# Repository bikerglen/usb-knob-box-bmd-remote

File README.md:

# usb-knob-box-bmd-remote

Blog post describing this project: https://bikerglen.com/blog/usb-knobs-that-double-as-a-blackmagic-remote/

If using the C# .NET app for testing, the product ID needs to be set to 0x0014 for the EFM8UB@ version or 0x0015 for the PIC18 version. This is inside the file Form1.cs.

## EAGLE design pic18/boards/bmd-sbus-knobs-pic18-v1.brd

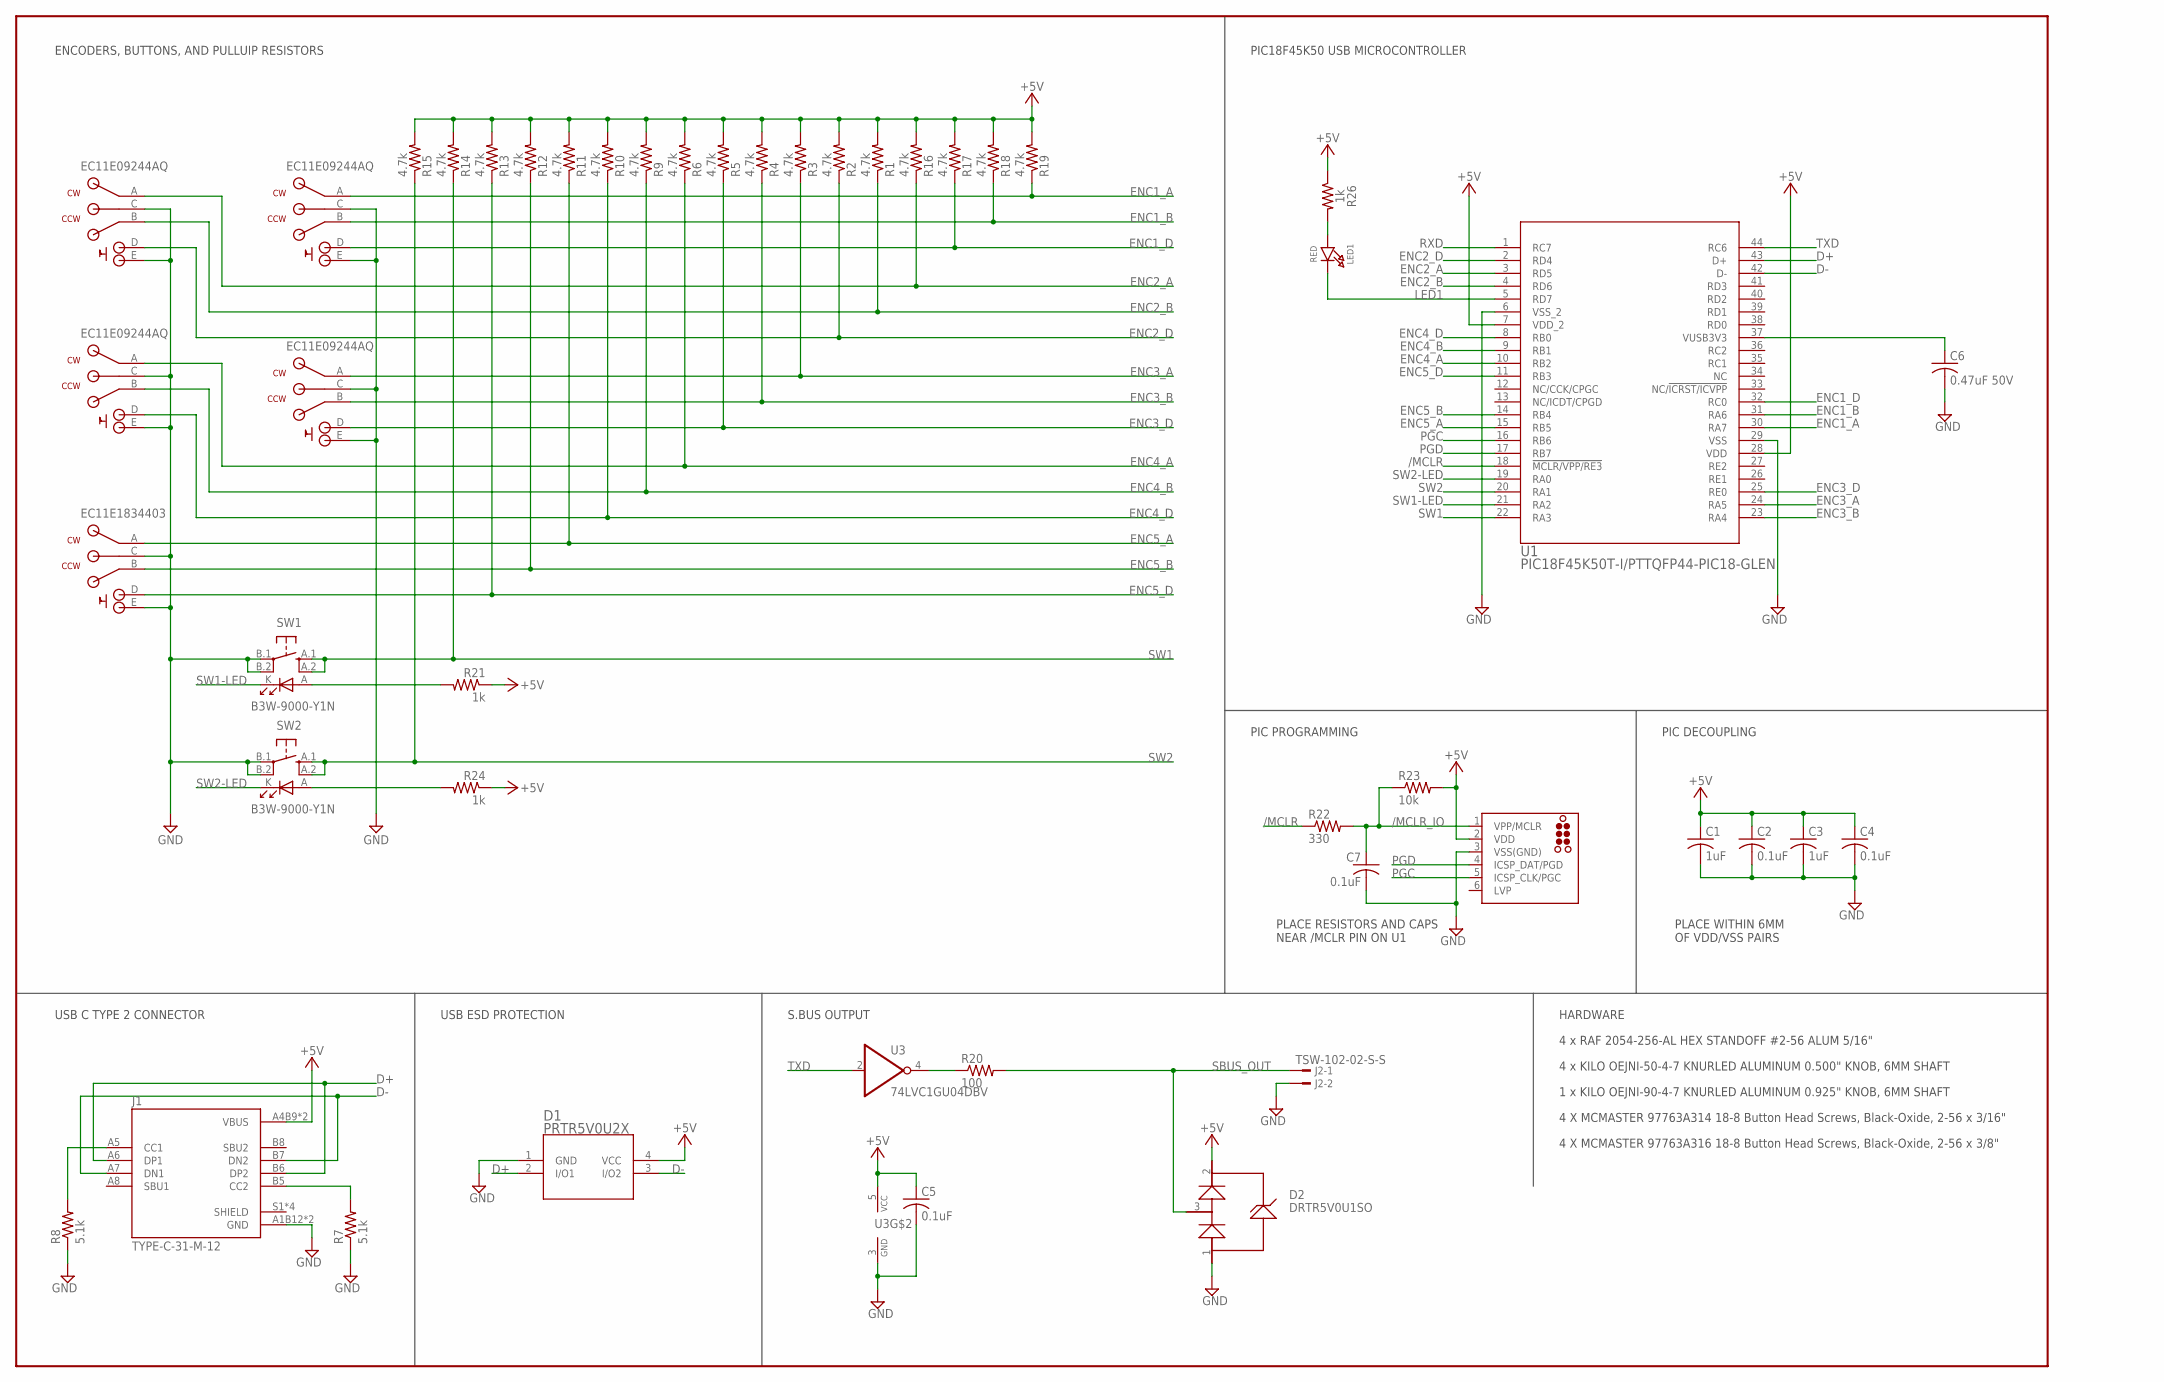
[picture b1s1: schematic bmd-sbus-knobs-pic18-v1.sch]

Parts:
C1, C3: 1uF; C0603K
C2, C4, C7: 0.1uF; C0603K
C5: 0.1uF; C0603
C6: 0.47uF 50V; C1206K; MFR_PART_NO C1206C474K5RACTU
D1: PRTR5V0U2X; SOT143B
D2: DRTR5V0U1SO; SOT23-3; MFR_PART_NO DRTR5V0U1SO
DEBUG: TC2030-MCP-NL
ENC1, ENC2, ENC3, ENC4, ENC5: EC11E15244B2
J1: TYPE-C-31-M-12; HRO_TYPE-C-31-M-12
J2: TSW-102-02-S-S
LED1: RED; CHIPLED_0805_NOOUTLINE
R1, R2, R3, R4, R5, R6, R9, R10, R11, R12, R13, R14, R15, R16, R17, R18, R19: 4.7k; R0603
R7, R8: 5.1k; R0603
R20: 100; R0603
R21, R24, R26: 1k; R0603
R22: 330; R0603
R23: 10k; R0603
SW1, SW2: B3W-9000-Y1N; OMRON-B3W-ILLUM-BUTTON
U1: PIC18F45K50T-I/PTTQFP44-PIC18-GLEN; TQFP44-PIC18-GLEN
U3: 74LVC1GU04DBV; SOT23-5

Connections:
+5V: C1.1, C2.1, C3.1, C4.1, C5.1, D1.4 (VCC), D2.2, DEBUG.2 (VDD), J1.A4B9 (VBUS), J1.B4A9 (VBUS), R1.2, R2.2, R3.2, R4.2, R5.2, R6.2, R9.2, R10.2, R11.2, R12.2, R13.2, R14.2, R15.2, R16.2, R17.2, R18.2, R19.2, R21.1, R23.2, R24.1, R26.1, U1.7 (VDD_2), U1.28 (VDD), U3.5 (VCC)
/MCLR: R22.1, U1.18 (!MCLR/VPP/RE3)
/MCLR_IO: C7.1, DEBUG.1 (VPP/MCLR), R22.2, R23.1
CC1: J1.A5 (CC1), R8.2
CC2: J1.B5 (CC2), R7.2
D+: D1.2 (I/O1), J1.A6 (DP1), J1.B6 (DP2), U1.43 (D+)
D-: D1.3 (I/O2), J1.A7 (DN1), J1.B7 (DN2), U1.42 (D-)
ENC1_A: ENC1.A, R19.1, U1.30 (RA7)
ENC1_B: ENC1.B, R18.1, U1.31 (RA6)
ENC1_D: ENC1.D, R17.1, U1.32 (RC0)
ENC2_A: ENC2.A, R16.1, U1.3 (RD5)
ENC2_B: ENC2.B, R1.1, U1.4 (RD6)
ENC2_D: ENC2.D, R2.1, U1.2 (RD4)
ENC3_A: ENC3.A, R3.1, U1.24 (RA5)
ENC3_B: ENC3.B, R4.1, U1.23 (RA4)
ENC3_D: ENC3.D, R5.1, U1.25 (RE0)
ENC4_A: ENC4.A, R6.1, U1.10 (RB2)
ENC4_B: ENC4.B, R9.1, U1.9 (RB1)
ENC4_D: ENC4.D, R10.1, U1.8 (RB0)
ENC5_A: ENC5.A, R11.1, U1.15 (RB5)
ENC5_B: ENC5.B, R12.1, U1.14 (RB4)
ENC5_D: ENC5.D, R13.1, U1.11 (RB3)
GND: C1.2, C2.2, C3.2, C4.2, C5.2, C6.2, C7.2, D1.1 (GND), D2.1 (3), DEBUG.3 (VSS(GND)), ENC1.C, ENC1.E, ENC2.C, ENC2.E, ENC3.C, ENC3.E, ENC4.C, ENC4.E, ENC5.C, ENC5.E, J1.A1B12 (GND), J1.B1A12 (GND), J2.2, R7.1, R8.1, SW1.B.1, SW1.B.2, SW2.B.1, SW2.B.2, U1.6 (VSS_2), U1.29 (VSS), U3.3 (GND)
LED1: LED1.C, U1.5 (RD7)
unnamed: R20.1, U3.4 (O)
unnamed: LED1.A, R26.2
unnamed: R21.2, SW1.A
unnamed: R24.2, SW2.A
PGC: DEBUG.5 (ICSP_CLK/PGC), U1.16 (RB6)
PGD: DEBUG.4 (ICSP_DAT/PGD), U1.17 (RB7)
RXD: U1.1 (RC7)
SBUS_OUT: D2.3 (1), J2.1, R20.2
SW1: R14.1, SW1.A.1, SW1.A.2, U1.22 (RA3)
SW1-LED: SW1.K, U1.21 (RA2)
SW2: R15.1, SW2.A.1, SW2.A.2, U1.20 (RA1)
SW2-LED: SW2.K, U1.19 (RA0)
TXD: U1.44 (RC6), U3.2 (I)
VUSB: C6.1, U1.37 (VUSB3V3)

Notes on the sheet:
EC11E09244AQ
EC11E1834403
PIC DECOUPLING
USB C TYPE 2 CONNECTOR
USB ESD PROTECTION
PIC PROGRAMMING
S.BUS OUTPUT
PLACE WITHIN 6MM OF VDD/VSS PAIRS
HARDWARE
4 x RAF 2054-256-AL HEX STANDOFF #2-56 ALUM 5/16"
4 x KILO OEJNI-50-4-7 KNURLED ALUMINUM 0.500" KNOB, 6MM SHAFT
1 x KILO OEJNI-90-4-7 KNURLED ALUMINUM 0.925" KNOB, 6MM SHAFT
4 X MCMASTER 97763A314 18-8 Button Head Screws, Black-Oxide, 2-56 x 3/16"
4 X MCMASTER 97763A316 18-8 Button Head Screws, Black-Oxide, 2-56 x 3/8"
PLACE RESISTORS AND CAPS NEAR /MCLR PIN ON U1
ENCODERS, BUTTONS, AND PULLUIP RESISTORS
PIC18F45K50 USB MICROCONTROLLER

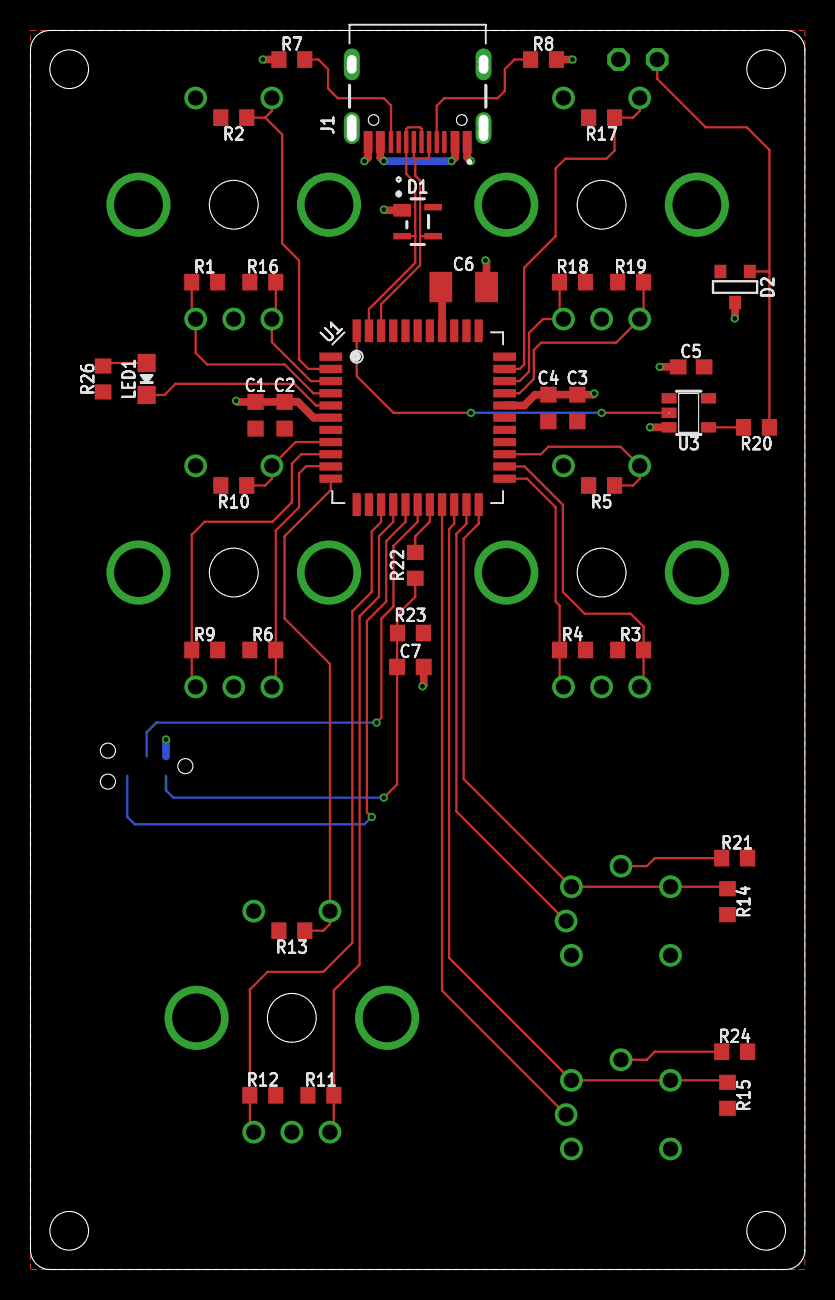
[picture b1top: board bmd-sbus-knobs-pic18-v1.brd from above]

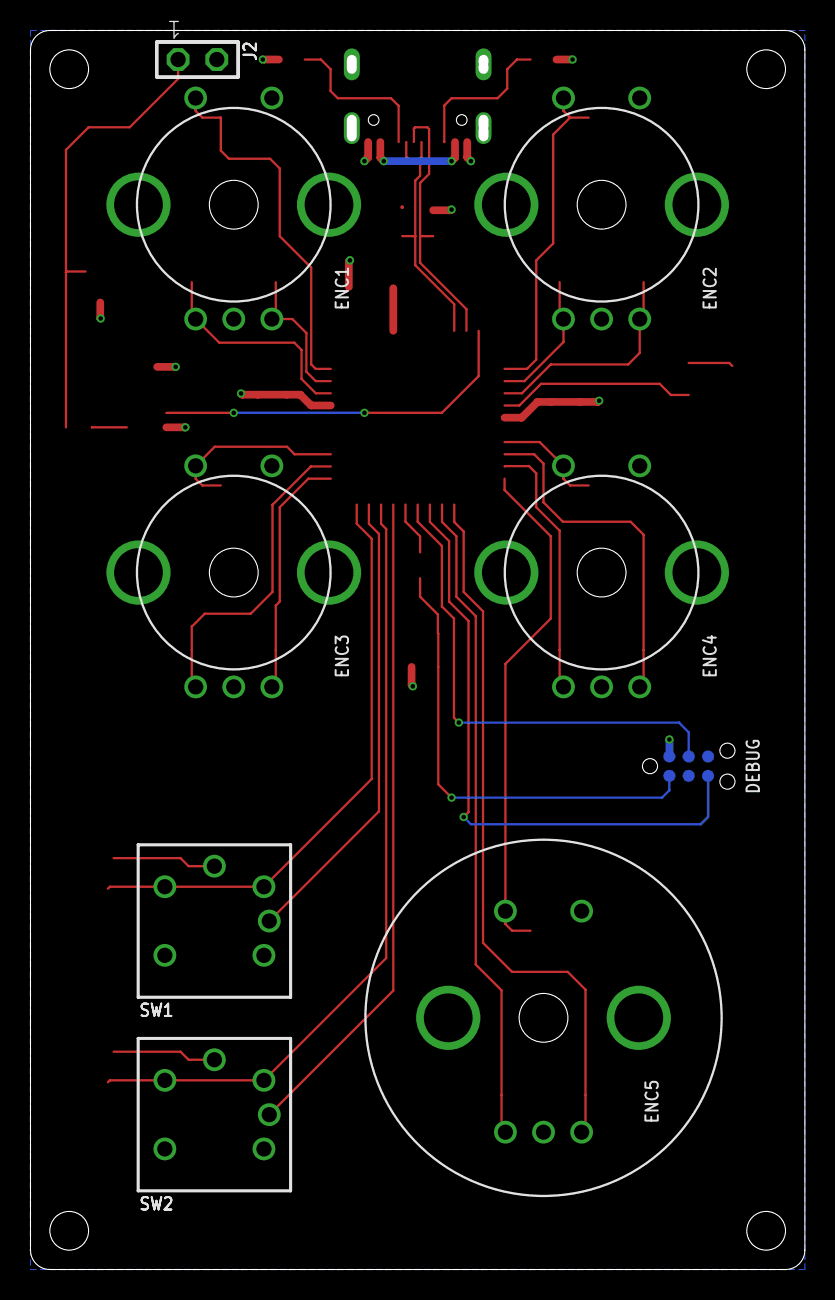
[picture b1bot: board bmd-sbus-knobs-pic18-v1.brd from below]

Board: 2 copper layers, 50.1 x 80.6 mm, 47 parts (9 on the bottom side), 37 nets.

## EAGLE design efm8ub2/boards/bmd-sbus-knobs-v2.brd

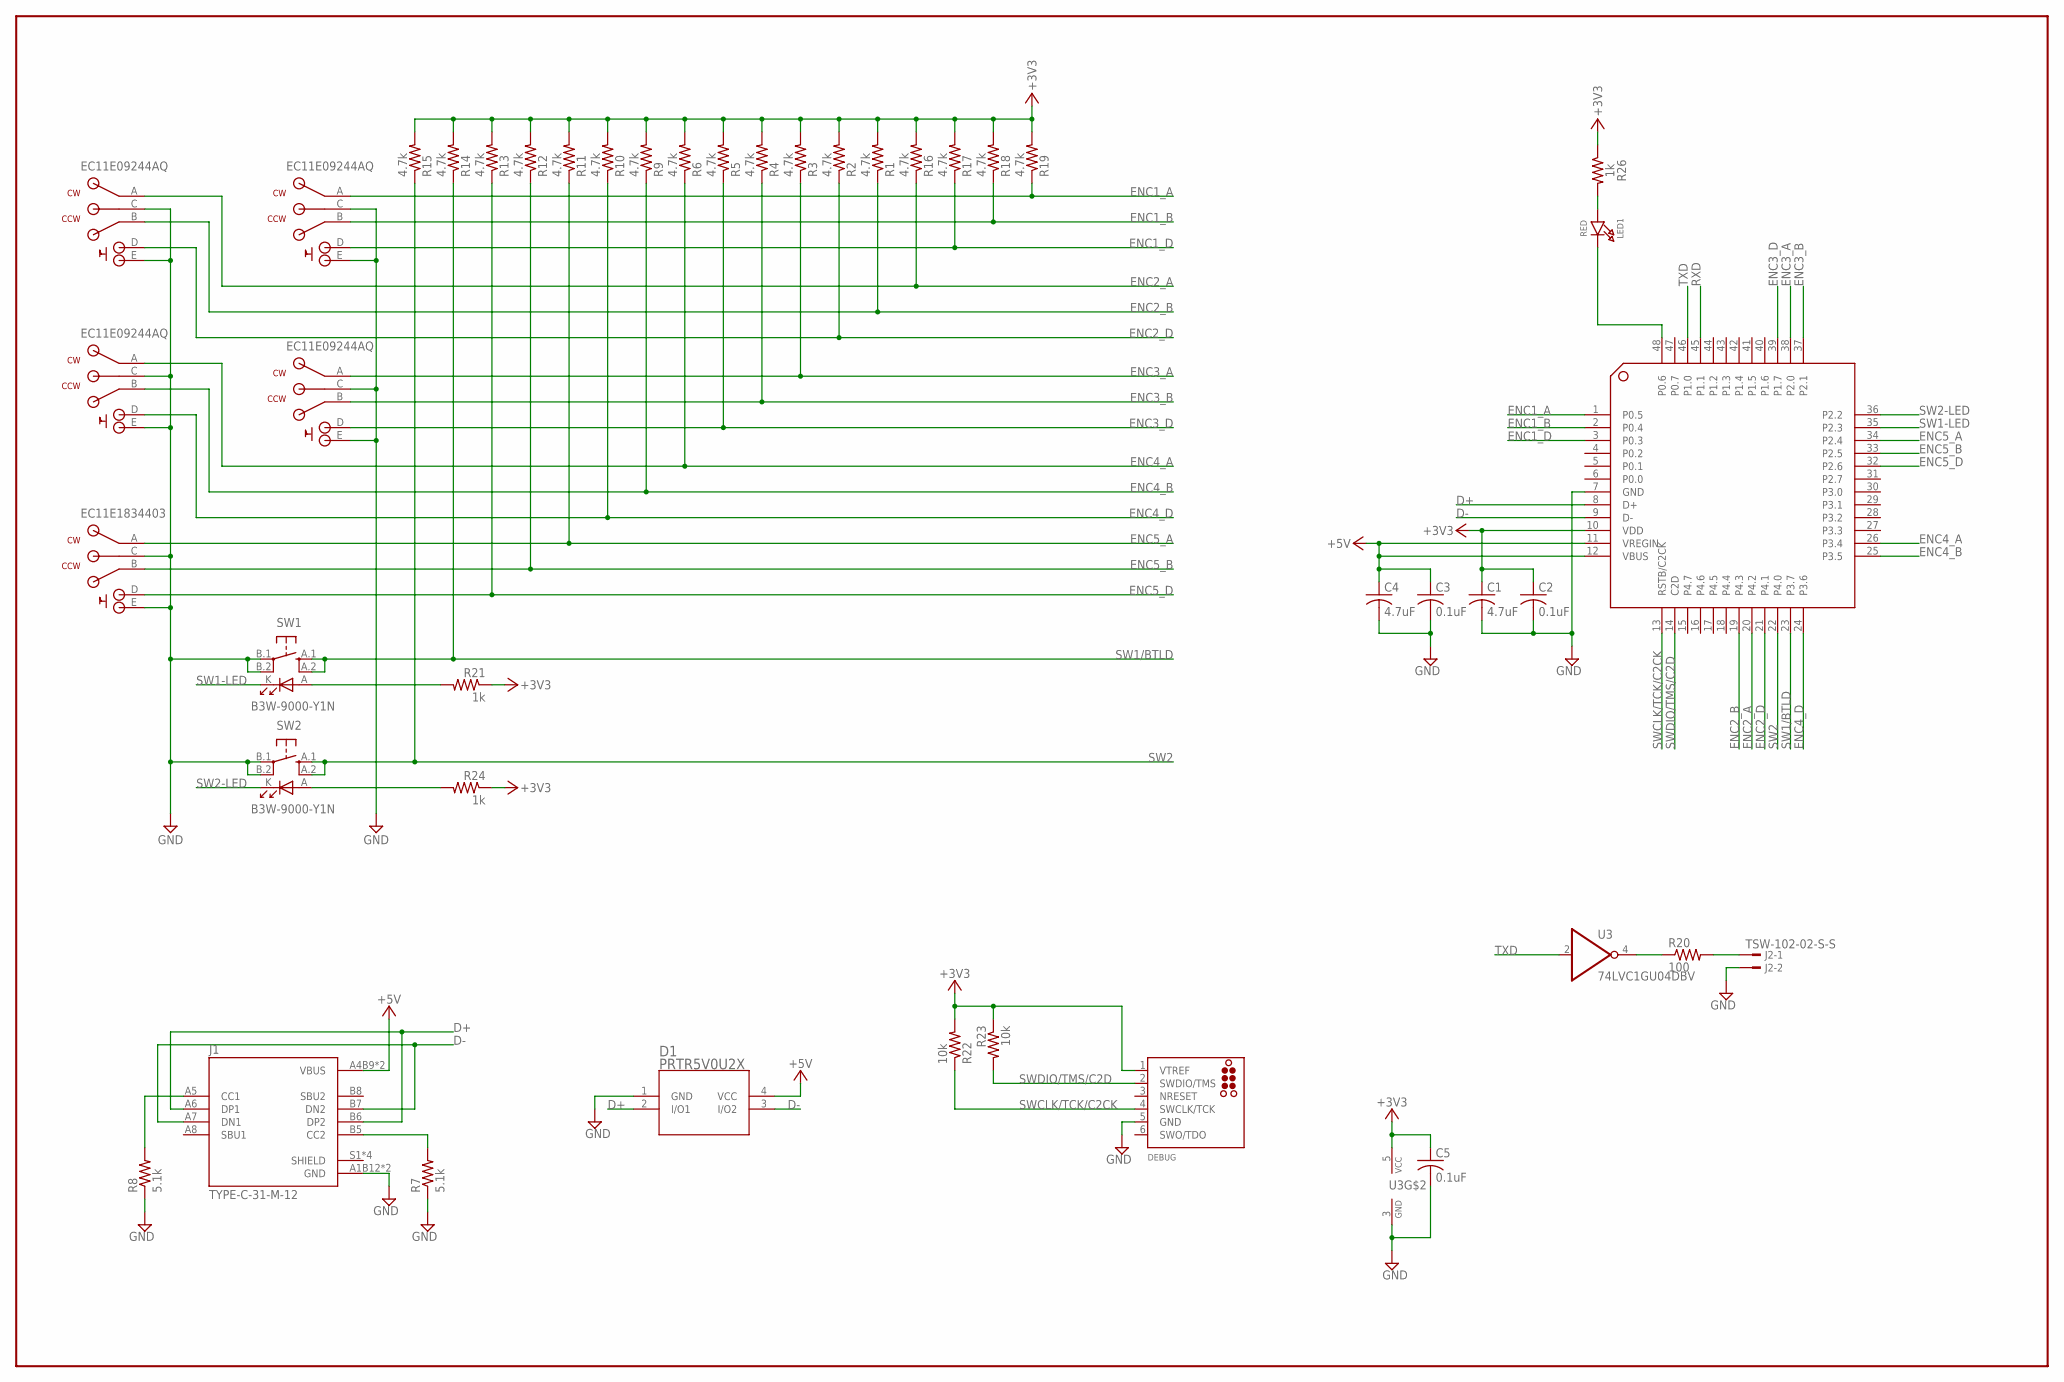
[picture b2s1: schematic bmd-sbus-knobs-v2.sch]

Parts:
C1, C4: 4.7uF; C0603K
C2, C3: 0.1uF; C0603K
C5: 0.1uF; C0603
D1: PRTR5V0U2X; SOT143B
DEBUG: TC2030-CTX-SWD; TC2030-MCP-NL
ENC1, ENC2, ENC3, ENC4, ENC5: EC11E15244B2
J1: TYPE-C-31-M-12; HRO_TYPE-C-31-M-12
J2: TSW-102-02-S-S
LED1: RED; CHIPLED_0805_NOOUTLINE
R1, R2, R3, R4, R5, R6, R9, R10, R11, R12, R13, R14, R15, R16, R17, R18, R19: 4.7k; R0603
R7, R8: 5.1k; R0603
R20: 100; R0603
R21, R24, R26: 1k; R0603
R22, R23: 10k; R0603
SW1, SW2: B3W-9000-Y1N; OMRON-B3W-ILLUM-BUTTON
U1: EFM8UB20F64G-B-QFP48; EFM8UB2-QFP48
U3: 74LVC1GU04DBV; SOT23-5

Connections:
+3V3: C1.1, C2.1, C5.1, DEBUG.1 (VTREF), R1.2, R2.2, R3.2, R4.2, R5.2, R6.2, R9.2, R10.2, R11.2, R12.2, R13.2, R14.2, R15.2, R16.2, R17.2, R18.2, R19.2, R21.1, R22.2, R23.1, R24.1, R26.1, U1.10 (VDD), U3.5 (VCC)
+5V: C3.1, C4.1, D1.4 (VCC), J1.A4B9 (VBUS), J1.B4A9 (VBUS), U1.11 (VREGIN), U1.12 (VBUS)
D+: D1.2 (I/O1), J1.A6 (DP1), J1.B6 (DP2), U1.8 (D+)
D-: D1.3 (I/O2), J1.A7 (DN1), J1.B7 (DN2), U1.9 (D-)
ENC1_A: ENC1.A, R19.1, U1.1 (P0.5)
ENC1_B: ENC1.B, R18.1, U1.2 (P0.4)
ENC1_D: ENC1.D, R17.1, U1.3 (P0.3)
ENC2_A: ENC2.A, R16.1, U1.20 (P4.2)
ENC2_B: ENC2.B, R1.1, U1.19 (P4.3)
ENC2_D: ENC2.D, R2.1, U1.21 (P4.1)
ENC3_A: ENC3.A, R3.1, U1.38 (P2.0)
ENC3_B: ENC3.B, R4.1, U1.37 (P2.1)
ENC3_D: ENC3.D, R5.1, U1.39 (P1.7)
ENC4_A: ENC4.A, R6.1, U1.26 (P3.4)
ENC4_B: ENC4.B, R9.1, U1.25 (P3.5)
ENC4_D: ENC4.D, R10.1, U1.24 (P3.6)
ENC5_A: ENC5.A, R11.1, U1.34 (P2.4)
ENC5_B: ENC5.B, R12.1, U1.33 (P2.5)
ENC5_D: ENC5.D, R13.1, U1.32 (P2.6)
GND: C1.2, C2.2, C3.2, C4.2, C5.2, D1.1 (GND), DEBUG.5 (GND), ENC1.C, ENC1.E, ENC2.C, ENC2.E, ENC3.C, ENC3.E, ENC4.C, ENC4.E, ENC5.C, ENC5.E, J1.A1B12 (GND), J1.B1A12 (GND), J2.2, R7.1, R8.1, SW1.B.1, SW1.B.2, SW2.B.1, SW2.B.2, U1.7 (GND), U3.3 (GND)
unnamed: J2.1, R20.2
unnamed: R20.1, U3.4 (O)
unnamed: LED1.A, R26.2
unnamed: R21.2, SW1.A
unnamed: R24.2, SW2.A
unnamed: LED1.C, U1.48 (P0.6)
unnamed: J1.B5 (CC2), R7.2
unnamed: J1.A5 (CC1), R8.2
NRESET: DEBUG.3 (NRESET)
RXD: U1.45 (P1.1)
SW1-LED: SW1.K, U1.35 (P2.3)
SW1/BTLD: R14.1, SW1.A.1, SW1.A.2, U1.23 (P3.7)
SW2: R15.1, SW2.A.1, SW2.A.2, U1.22 (P4.0)
SW2-LED: SW2.K, U1.36 (P2.2)
SWCLK/TCK/C2CK: DEBUG.4 (SWCLK/TCK), R22.1, U1.13 (RSTB/C2CK)
SWDIO/TMS/C2D: DEBUG.2 (SWDIO/TMS), R23.2, U1.14 (C2D)
TXD: U1.46 (P1.0), U3.2 (I)

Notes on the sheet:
EC11E09244AQ
EC11E1834403

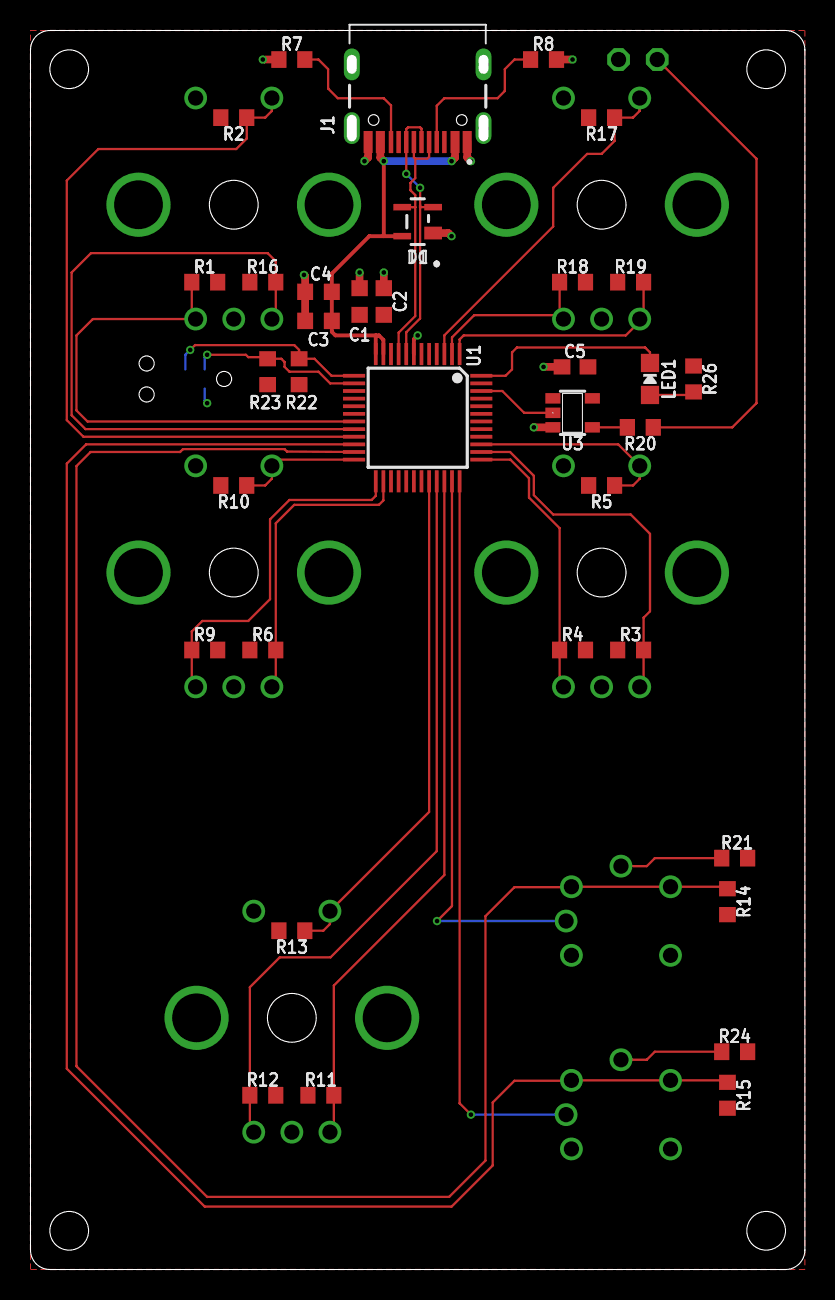
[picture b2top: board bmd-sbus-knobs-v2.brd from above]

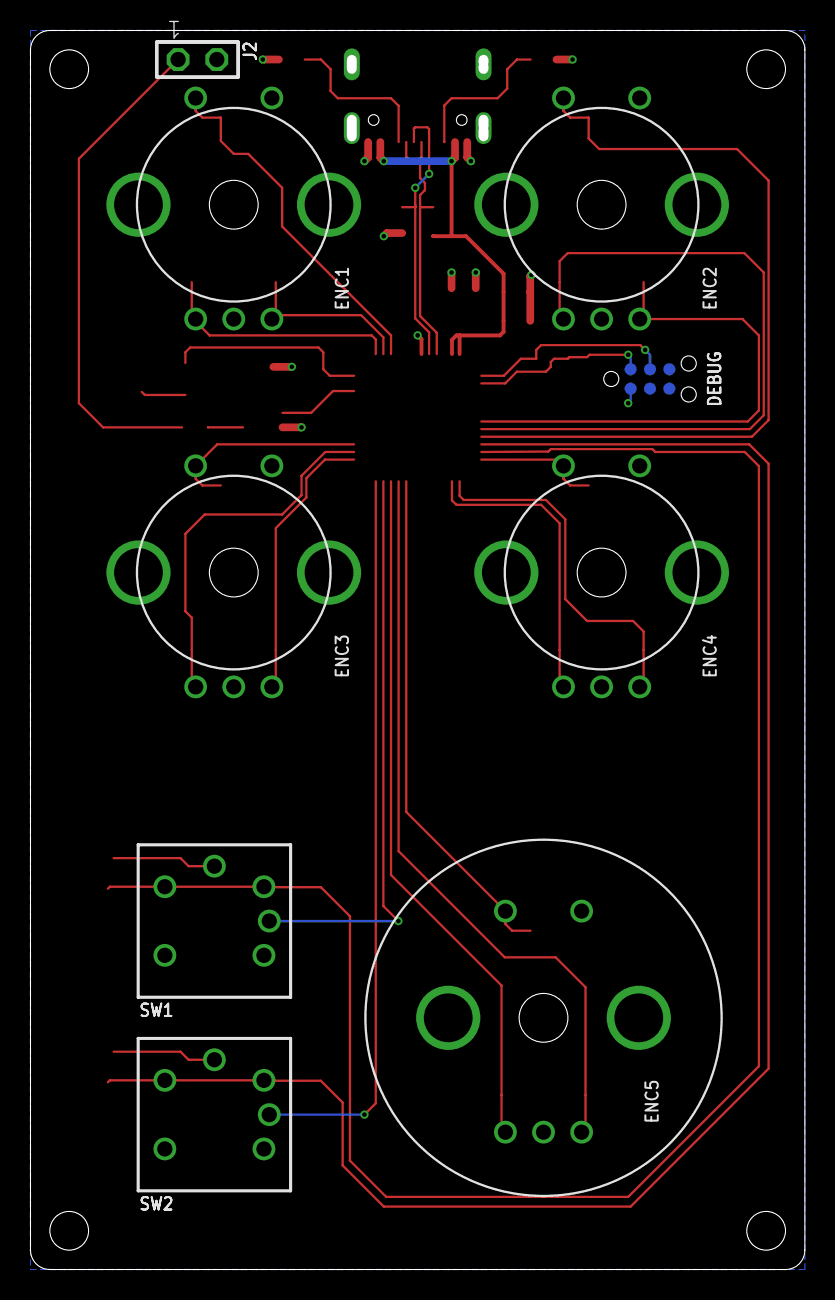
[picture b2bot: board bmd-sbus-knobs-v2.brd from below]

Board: 2 copper layers, 50.1 x 80.6 mm, 44 parts (9 on the bottom side), 35 nets.

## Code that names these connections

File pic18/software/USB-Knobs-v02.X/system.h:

/*******************************************************************************
Copyright 2016 Microchip Technology Inc. (www.microchip.com)

Licensed under the Apache License, Version 2.0 (the "License");
you may not use this file except in compliance with the License.
You may obtain a copy of the License at

    http://www.apache.org/licenses/LICENSE-2.0

Unless required by applicable law or agreed to in writing, software
distributed under the License is distributed on an "AS IS" BASIS,
WITHOUT WARRANTIES OR CONDITIONS OF ANY KIND, either express or implied.
See the License for the specific language governing permissions and
limitations under the License.

To request to license the code under the MLA license (www.microchip.com/mla_license), 
please contact mla_licensing@microchip.com
*******************************************************************************/

#ifndef SYSTEM_H
#define SYSTEM_H

#include <xc.h>
#include <stdbool.h>

#include "fixed_address_memory.h"

#define MAIN_RETURN void

// 250 Hz timer 0 load / reload value
// dec2hex(65535-12e6/16/250) = 0xF447
// #define TMR0_RELOAD_VALUE 0xF447

// 8333 Hz timer 0 load / reload value
// dec2hex(round(65535-12e6/16/8333)) = 0xFFA5
#define TMR0_RELOAD_VALUE 0xFFA5

// 250 Hz timer 2 period value
// dec2hex(12e6/16/12/250-1)
#define TMR2_PERIOD 0xF9

// GPIO input pins
#define ENC1_A   (PORTAbits.RA7 ? 1 : 0)
#define ENC1_B   (PORTAbits.RA6 ? 1 : 0)
#define ENC1_SW  (PORTCbits.RC0 ? 0 : 1)
#define ENC2_A   (PORTDbits.RD5 ? 1 : 0)
#define ENC2_B   (PORTDbits.RD6 ? 1 : 0)
#define ENC2_SW  (PORTDbits.RD4 ? 0 : 1)
#define ENC3_A   (PORTAbits.RA5 ? 1 : 0)
#define ENC3_B   (PORTAbits.RA4 ? 1 : 0)
#define ENC3_SW  (PORTEbits.RE0 ? 0 : 1)
#define ENC4_A   (PORTBbits.RB2 ? 1 : 0)
#define ENC4_B   (PORTBbits.RB1 ? 1 : 0)
#define ENC4_SW  (PORTBbits.RB0 ? 0 : 1)
#define ENC5_A   (PORTBbits.RB5 ? 1 : 0)
#define ENC5_B   (PORTBbits.RB4 ? 1 : 0)
#define ENC5_SW  (PORTBbits.RB3 ? 0 : 1)
#define SW1      (PORTAbits.RA3 ? 0 : 1)
#define SW2      (PORTAbits.RA1 ? 0 : 1)

// GPIO output pins
#define USER_LED LATDbits.LATD7
#define SW1_LED  LATAbits.LATA2
#define SW2_LED  LATAbits.LATA0

// led states
#define LED_ON   0
#define LED_OFF  1


/*** System States **************************************************/
typedef enum {
    SYSTEM_STATE_USB_START,
    SYSTEM_STATE_USB_SUSPEND,
    SYSTEM_STATE_USB_RESUME
} SYSTEM_STATE;

/*********************************************************************
* Function: void SYSTEM_Initialize( SYSTEM_STATE state )
*
* Overview: Initializes the system.
*
* PreCondition: None
*
* Input:  SYSTEM_STATE - the state to initialize the system into
*
* Output: None
*
********************************************************************/
void SYSTEM_Initialize( SYSTEM_STATE state );


/*********************************************************************
* Function: void SYSTEM_Tasks(void)
*
* Overview: Runs system level tasks that keep the system running
*
* PreCondition: System has been initalized with SYSTEM_Initialize()
*
* Input: None
*
* Output: None
*
********************************************************************/
//void SYSTEM_Tasks(void);
#define SYSTEM_Tasks()

void TMR0_Initialize (void);
void TMR0_InterruptHandler (void);

void TMR2_Initialize (void);
void TMR2_InterruptHandler (void);

#endif //SYSTEM_H

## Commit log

2021-05-17 initial checkin
2021-05-17 added ide projects
2021-05-17 add C# dot net app for testing

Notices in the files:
parts and their libraries:
tag-connect: ©2009 ROFA.cz - modified and updated by Robert Darlington ‹rdarlington@gmail.com›
microbuilder: This work is placed in the public domain, and may be freely used for commercial and non-commercial work with the following conditions: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
